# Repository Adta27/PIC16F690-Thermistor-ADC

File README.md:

# PIC16F690 Thermistor ADC Temperature Display

This project is a temperature sensing circuit built using a PIC16F690 microcontroller and assembly language. It uses a thermistor as an analog input, reads the temperature-related voltage through the PIC16F690 ADC, and displays the temperature level using 8 LEDs.

The goal of this project was to learn how analog sensors, ADC conversion, microcontroller programming, and PCB design work together in an embedded system.

## What It Does

- Reads temperature changes using a thermistor voltage divider circuit
- Uses the PIC16F690 ADC on RB4 / AN10 / physical pin 13
- Converts the analog thermistor voltage into a digital ADC value
- Displays the temperature level using LEDs connected to PORTC
- Uses assembly language to configure the ADC, read values, and control outputs
- Includes schematic and PCB design files

## How It Works

The thermistor changes resistance when the temperature changes. This changes the voltage going into the PIC16F690 ADC pin.

The PIC16F690 reads this analog voltage using its ADC module. The program stores the ADC result and compares it to different threshold values. Depending on the ADC value, different LEDs turn on to show the temperature range.

In this circuit, a higher ADC value means colder temperature, and a lower ADC value means hotter temperature.

## LED Output

The LEDs are connected to PORTC:

| PIC Pin | Port Pin | LED |
|---|---|---|
| Pin 9 | RC7 | LED 4 Yellow |
| Pin 8 | RC6 | LED 5 Green |
| Pin 5 | RC5 | LED 8 Blue |
| Pin 6 | RC4 | LED 7 Blue |
| Pin 7 | RC3 | LED 6 Green |
| Pin 14 | RC2 | LED 3 Yellow |
| Pin 15 | RC1 | LED 2 Red |
| Pin 16 | RC0 | LED 1 Red |

## Code

The full assembly source code is in:

```text
code/thermistor_adc.asm

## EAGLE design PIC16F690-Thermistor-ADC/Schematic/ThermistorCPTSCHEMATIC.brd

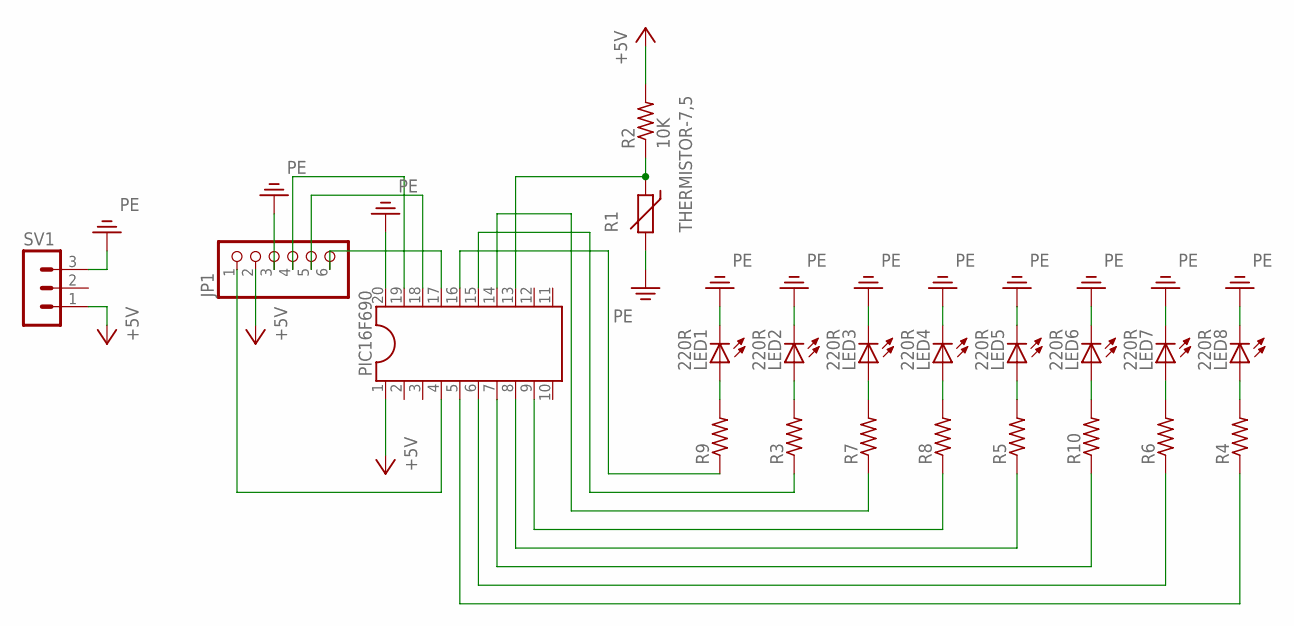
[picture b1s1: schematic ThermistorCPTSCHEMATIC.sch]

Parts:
JP1: PINHD-1X6; 1X06
LED1, LED2, LED3, LED4, LED5, LED6, LED7, LED8: 220R; LED5MM
PIC16F690: DIL20
R1: THERMISTOR-7,5; R-7,5
R2: 10K; 0207/10
R3, R4, R5, R6, R7, R8, R9, R10: R-US_0207/10; 0207/10
SV1: MA03-1

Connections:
+5V: JP1.2, PIC16F690.1, R2.2, SV1.1
unnamed: PIC16F690.14, R7.1
unnamed: JP1.4, PIC16F690.19
unnamed: JP1.5, PIC16F690.18
unnamed: JP1.6, PIC16F690.17
unnamed: LED7.A, R6.2
unnamed: LED8.A, R4.2
unnamed: LED6.A, R10.2
unnamed: LED5.A, R5.2
unnamed: LED4.A, R8.2
unnamed: LED3.A, R7.2
unnamed: LED2.A, R3.2
unnamed: LED1.A, R9.2
unnamed: PIC16F690.16, R9.1
unnamed: PIC16F690.15, R3.1
unnamed: PIC16F690.9, R8.1
unnamed: PIC16F690.8, R5.1
unnamed: JP1.1, PIC16F690.4
unnamed: PIC16F690.7, R10.1
unnamed: PIC16F690.6, R6.1
unnamed: PIC16F690.5, R4.1
unnamed: PIC16F690.13, R1.1, R2.1
PE: JP1.3, LED1.K (C), LED2.K (C), LED3.K (C), LED4.K (C), LED5.K (C), LED6.K (C), LED7.K (C), LED8.K (C), PIC16F690.20, R1.2, SV1.3

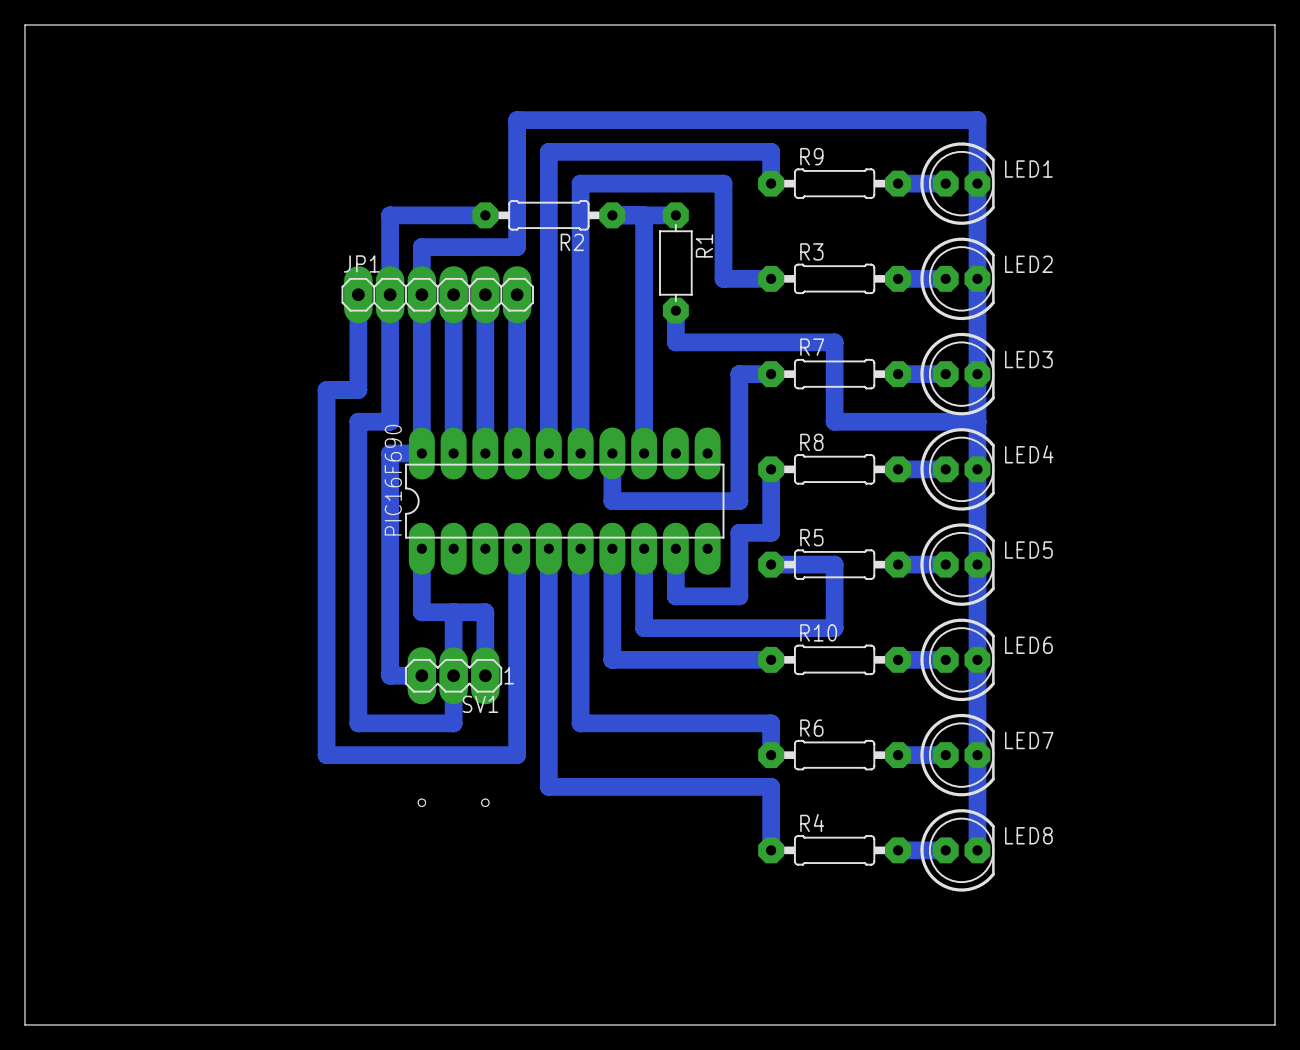
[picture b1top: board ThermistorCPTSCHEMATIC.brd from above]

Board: 2 copper layers, 100.0 x 80.0 mm, 21 parts (0 on the bottom side), 23 nets.
